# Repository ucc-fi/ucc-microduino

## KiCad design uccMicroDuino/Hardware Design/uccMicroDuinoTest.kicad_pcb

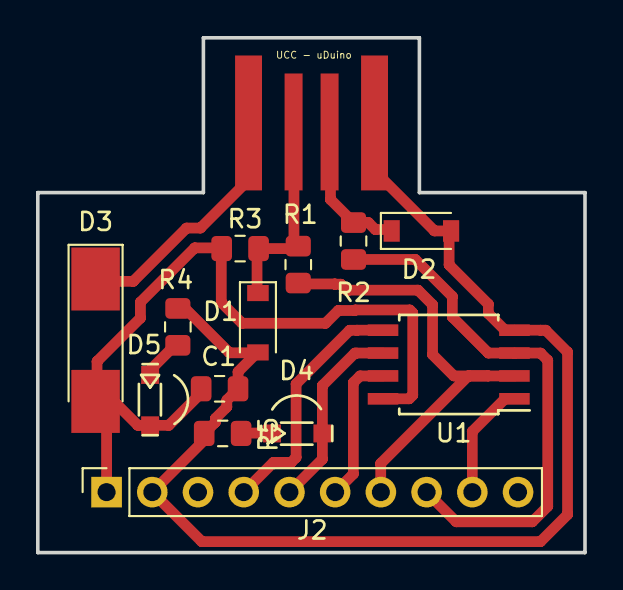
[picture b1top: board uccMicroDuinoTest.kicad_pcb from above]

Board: 2 copper layers, 30.4 x 28.6 mm, 14 parts (0 on the bottom side), 13 nets.

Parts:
C1: 0.1u; C_0805_2012Metric_Pad1.15x1.40mm_HandSolder
D1, D2: 3.6V 1/2mW; D_SOD-123
D3: PMLL4148L; D_MELF_Handsoldering
D4: Led Green; led
D5: Led Red; led
J1: USB_PCB_A; USB_A_UCC
J2: Header; PinSocket_1x10_P2.54mm_Vertical
R1, R2: 68Ω 5% 1/8W; R_0805_2012Metric_Pad1.15x1.40mm_HandSolder
R3: 1.5KΩ 5% 1/8W; R_0805_2012Metric_Pad1.15x1.40mm_HandSolder
R4, R5: 330Ω 5% 1/8W; R_0805_2012Metric_Pad1.15x1.40mm_HandSolder
U1: ATtiny85-20SU; SOIJ-8_5.3x5.3mm_P1.27mm

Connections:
+5V: C1.1, D3.2, D5.2, J2.1, R3.1, U1.8
GND: C1.2, D1.2, D2.2, J1.4, J2.2, R4.2, R5.1, U1.4
unnamed: D1.1, J1.2, R1.2, R3.2
unnamed: D2.1, J1.3, R2.2
unnamed: D3.1, J1.1
unnamed: D4.1, R5.2
unnamed: D4.2, J2.5, U1.6
unnamed: D5.1, R4.1
unnamed: J2.4, U1.5
unnamed: J2.6, U1.7
unnamed: J2.7, R1.1, U1.2
unnamed: J2.8, R2.1, U1.3
unnamed: J2.9, U1.1

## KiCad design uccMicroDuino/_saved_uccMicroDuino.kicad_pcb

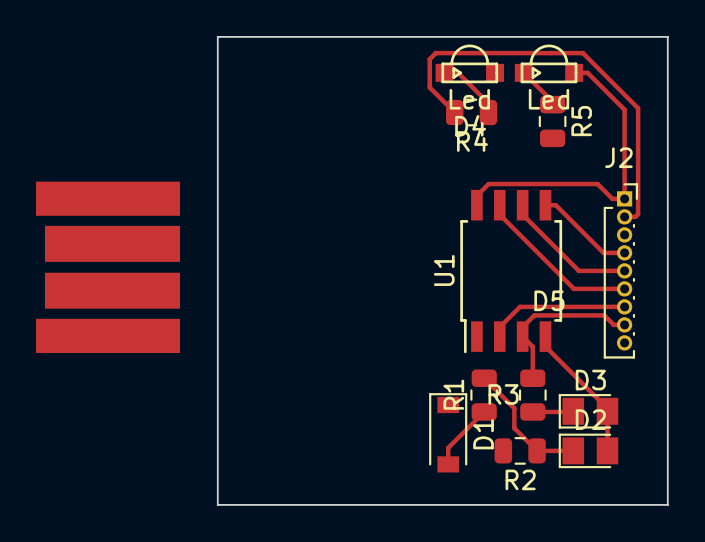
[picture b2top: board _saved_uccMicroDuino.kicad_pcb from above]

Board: 2 copper layers, 25.0 x 26.0 mm, 13 parts (0 on the bottom side), 13 nets.

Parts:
D1: DIODE; D_SOD-123
D2, D3: 3,6v; D_MicroMELF
D4: LED_GREEN; LedSmd1221SYGCS530XXTR8
D5: LED_RED; LedSmd1221SYGCS530XXTR8
J1: USB_A_PLUG; usb-PCB
J2: Conn_01x09_Female; PinSocket_1x09_P1.00mm_Vertical
R1: 1K5; R_0805_2012Metric
R2, R3: 68; R_0805_2012Metric
R4, R5: 470; R_0805_2012Metric
U1: ATtiny85-20SU; SOIJ-8_5.3x5.3mm_P1.27mm

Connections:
+5V: D1.2, D5.2, J2.1, R1.1, U1.8
GND: D2.2, D3.2, J1.4, J2.2, R4.2, R5.2, U1.4
unnamed: D1.1, J1.1
unnamed: D2.1, J1.2, R1.2, R2.1
unnamed: D3.1, J1.3, R3.1
unnamed: D4.1, R4.1
unnamed: D4.2, J2.5, U1.6
unnamed: D5.1, R5.1
unnamed: J2.4, U1.5
unnamed: J2.6, U1.7
unnamed: J2.7, R2.2, U1.2
unnamed: J2.8, R3.2, U1.3
unnamed: J2.9, U1.1

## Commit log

2018-09-18 Se crea repo de proyecto Kicad de UccMicroDuino
2018-10-03 Versión definitiva
2018-10-03 Presupuestos Prototipado
2018-10-03 presupuestos en formato excel
2018-10-05 Agregado modelo 3D y cerrado el poligono de placa
2018-10-05 se agrego render de la placa
